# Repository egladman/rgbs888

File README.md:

# rgbs888

Passive 24-bit RGBs adapter for Raspberry-Pi B+

## Bill of Materials
- 1 2x20 2.5mm Female Header
- 4 RCA right angle female pcb mount connectors
- 1 DB15 female connector *Optional*
- 1 120 ohm 0805 resistor *We don't care about the tolerance as much, so 5% would be sufficient*
- 3 549 ohm 0805 1% tolerance resistor
- 3 1.1K ohm 0805 1% tolerance resistor
- 3 2.21K ohm 0805 1% tolerance resistor
- 3 4.42K ohm 0805 1% tolerance resistor
- 3 8.87K ohm 0805 1% tolerance resistor
- 3 17.8K ohm 0805 1% tolerance resistor
- 3 35.7K ohm 0805 1% tolerance resistor
- 3 71.5K ohm 0805 1% tolerance resistor

```
MOUSER PART NUMBERS
========================

Connectors
806-KLPX-0848A-2-B
523-7HDE15SDH4RHNVGA

Resistors
667-ERJ-6GEYJ121V
652-CR0805FX-5490ELF
603-RC0805FR-131K1L
603-RC0805FR-072K21L
667-ERJ-6ENF4421V
667-ERJ-6ENF8871V
667-ERJ-6ENF1782V
667-ERJ-6ENF3572V
667-ERJ-6ENF7152V
```

## License

Copyright © 2020 Eli Gladman 

This document and the related databases are free: you can redistribute it and/or modify it under the terms of the GNU General Public License as published by the Free Software Foundation, either version 3 of the License, or any later version. This document and the related databases are distributed in the hope that it will be useful, but WITHOUT ANY WARRANTY; without even the implied warranty of MERCHANTABILITY or FITNESS FOR A PARTICULAR PURPOSE. See the GNU General Public License for more details. You should have received a copy of the GNU General Public License along with this database. If not, see http://www.gnu.org/licenses/

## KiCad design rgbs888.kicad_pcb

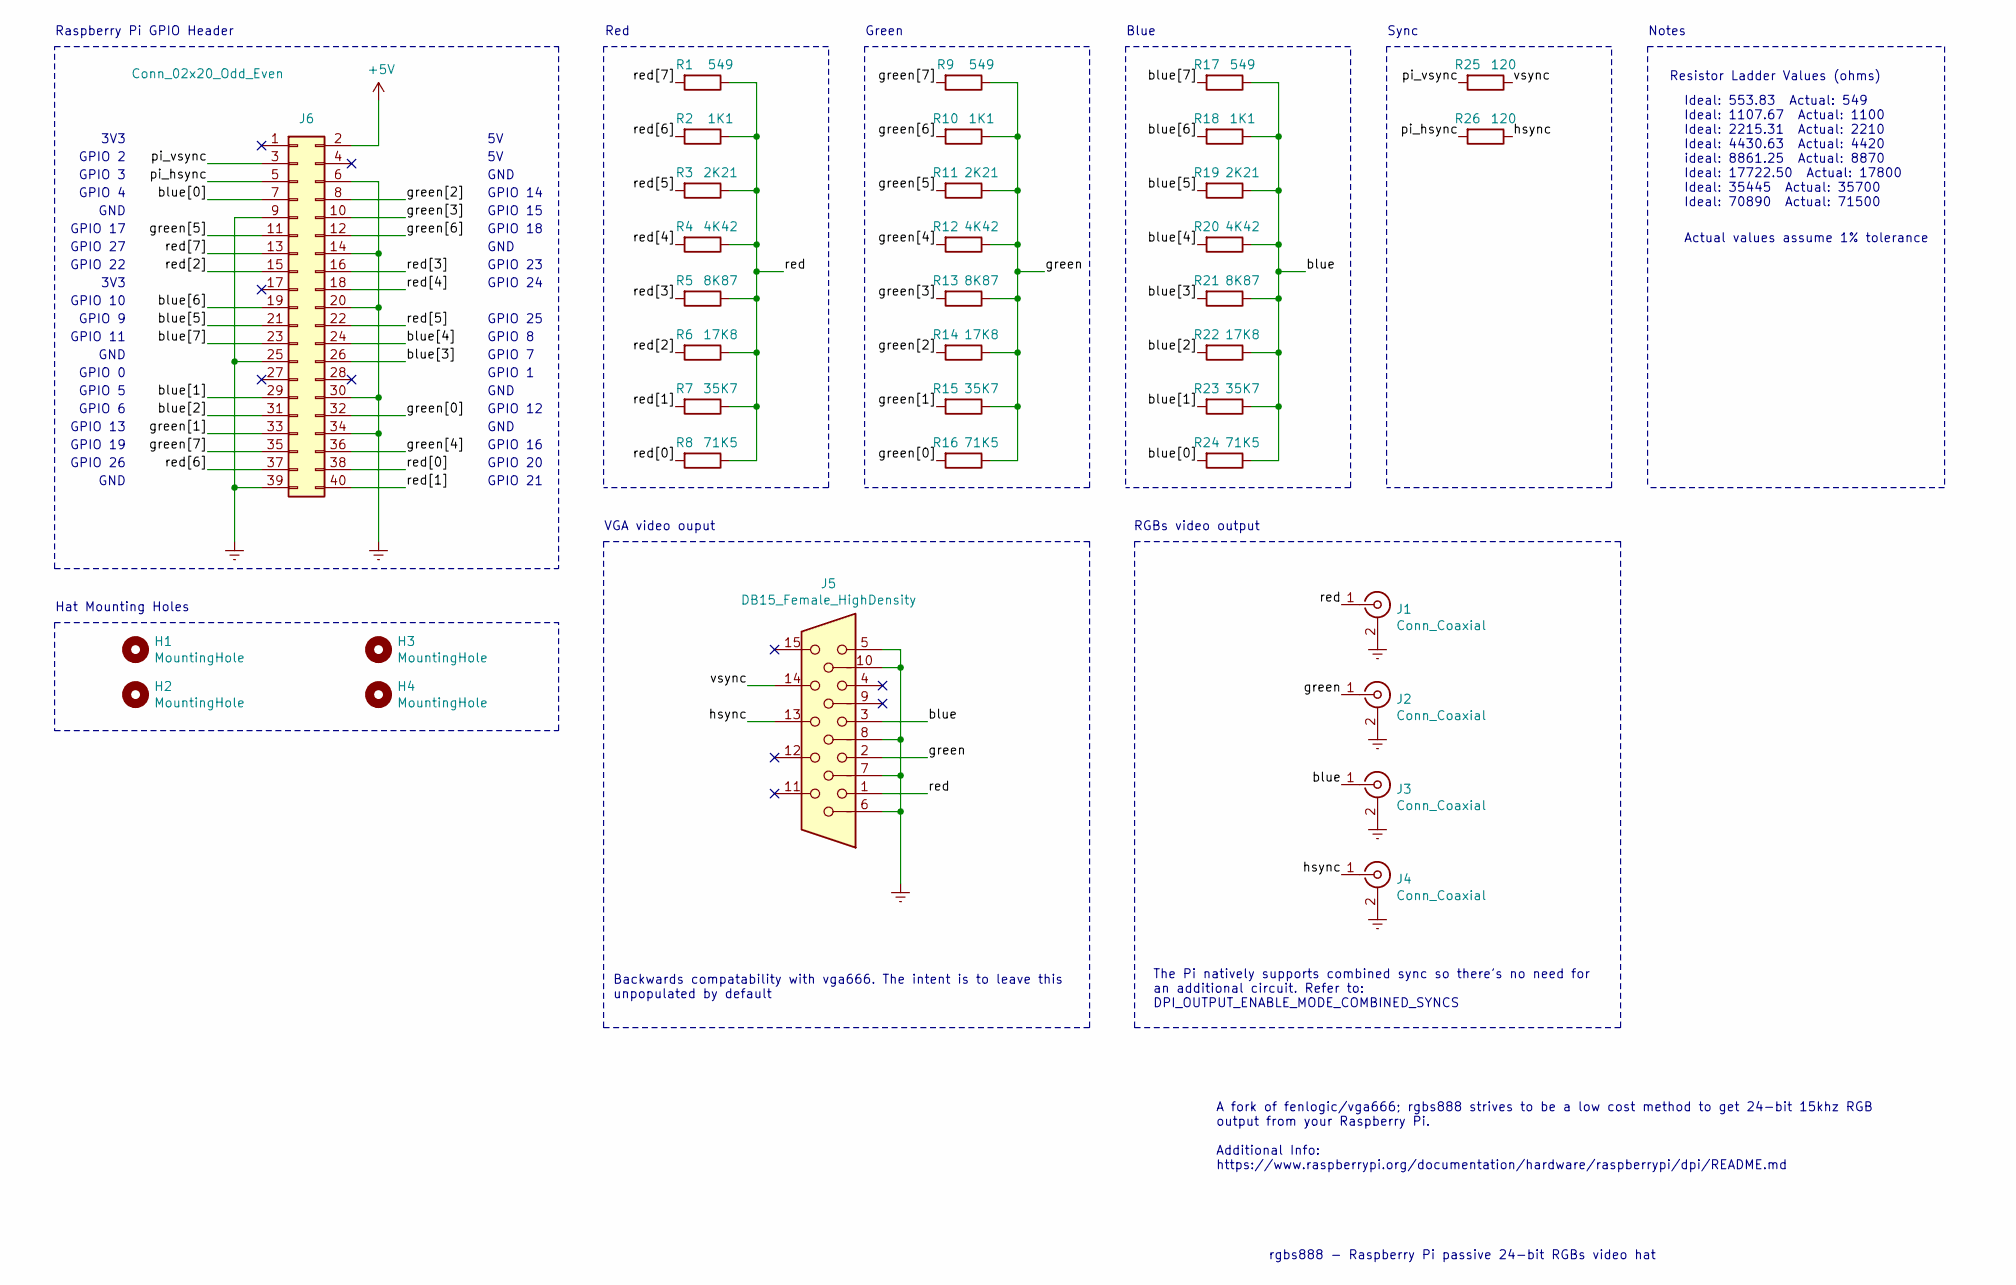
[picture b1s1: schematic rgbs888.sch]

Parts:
H1, H2, H3, H4: MountingHole; Pi_Hat_Mounting_Hole
J1, J2, J3, J4: Conn_Coaxial; RCA_Female_THT-1_Horizontal
J5: DB15_Female_HighDensity; DB15_Female_THT
J6: Conn_02x20_Odd_Even; PinHeader_2x20_P2.54mm_Vertical
R1, R9, R17: 549; R_0805_2012Metric_Pad1.15x1.40mm_HandSolder
R2, R10, R18: 1K1; R_0805_2012Metric_Pad1.15x1.40mm_HandSolder
R3, R11, R19: 2K21; R_0805_2012Metric_Pad1.15x1.40mm_HandSolder
R4, R12, R20: 4K42; R_0805_2012Metric_Pad1.15x1.40mm_HandSolder
R5, R13, R21: 8K87; R_0805_2012Metric_Pad1.15x1.40mm_HandSolder
R6, R14, R22: 17K8; R_0805_2012Metric_Pad1.15x1.40mm_HandSolder
R7, R15, R23: 35K7; R_0805_2012Metric_Pad1.15x1.40mm_HandSolder
R8, R16, R24: 71K5; R_0805_2012Metric_Pad1.15x1.40mm_HandSolder
R25, R26: 120; R_0805_2012Metric_Pad1.15x1.40mm_HandSolder

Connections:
+5V: J6.2
/blue: J3.1 (In), J5.3, R17.1, R18.1, R19.1, R20.1, R21.1, R22.1, R23.1, R24.1
/blue[0]: J6.7, R24.2
/blue[1]: J6.29, R23.2
/blue[2]: J6.31, R22.2
/blue[3]: J6.26, R21.2
/blue[4]: J6.24, R20.2
/blue[5]: J6.21, R19.2
/blue[6]: J6.19, R18.2
/blue[7]: J6.23, R17.2
/green: J2.1 (In), J5.2, R9.1, R10.1, R11.1, R12.1, R13.1, R14.1, R15.1, R16.1
/green[0]: J6.32, R16.2
/green[1]: J6.33, R15.2
/green[2]: J6.8, R14.2
/green[3]: J6.10, R13.2
/green[4]: J6.36, R12.2
/green[5]: J6.11, R11.2
/green[6]: J6.12, R10.2
/green[7]: J6.35, R9.2
/hsync: J4.1 (In), J5.13, R26.1
/pi_hsync: J6.5, R26.2
/pi_vsync: J6.3, R25.2
/red: J1.1 (In), J5.1, R1.1, R2.1, R3.1, R4.1, R5.1, R6.1, R7.1, R8.1
/red[0]: J6.38, R8.2
/red[1]: J6.40, R7.2
/red[2]: J6.15, R6.2
/red[3]: J6.16, R5.2
/red[4]: J6.18, R4.2
/red[5]: J6.22, R3.2
/red[6]: J6.37, R2.2
/red[7]: J6.13, R1.2
/vsync: J5.14, R25.1
Earth: J1.2 (Ext), J2.2 (Ext), J3.2 (Ext), J4.2 (Ext), J5.5, J5.6, J5.7, J5.8, J5.10, J6.6, J6.9, J6.14, J6.20, J6.25, J6.30, J6.34, J6.39

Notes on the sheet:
rgbs888 - Raspberry Pi passive 24-bit RGBs video hat
RGBs video output
Red
Raspberry Pi GPIO Header
Hat Mounting Holes
GPIO 21
GPIO 20
GPIO 16
GPIO 12
GPIO 7
GPIO 8
GPIO 25
GPIO 24
GPIO 23
GPIO 18
GPIO 15
GPIO 14
GND
GPIO 1
GPIO 26
GPIO 19
GPIO 13
GPIO 6
GPIO 5
GPIO 0
GPIO 11
GPIO 9
GPIO 10
3V3
GPIO 22
GPIO 27
GPIO 17
GPIO 4
GPIO 3
GPIO 2
Green
Blue
Actual values assume 1% tolerance
The Pi natively supports combined sync so there's no need for an additional circuit. Refer to: DPI_OUTPUT_ENABLE_MODE_COMBINED_SYNCS
Sync

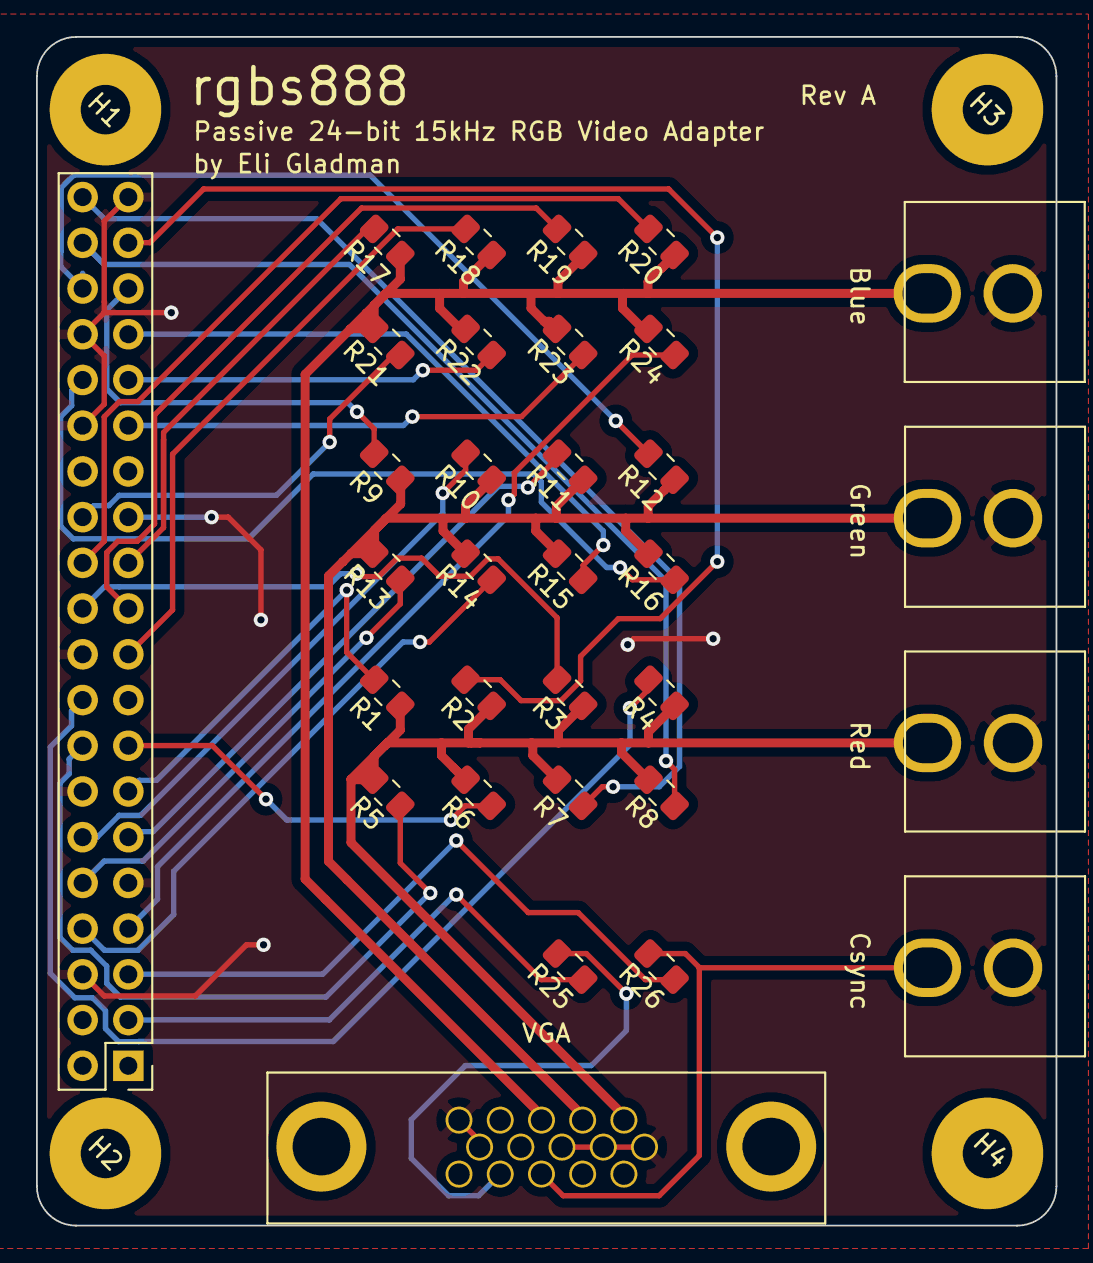
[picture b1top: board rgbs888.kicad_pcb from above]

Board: 2 copper layers, 56.6 x 66.0 mm, 36 parts (0 on the bottom side), 32 nets.

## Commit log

2020-07-13 Rev A set to fab shop
